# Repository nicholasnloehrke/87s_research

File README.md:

# Code and hardware design files

## Block diagram

### Overall system

> TODO

### Controller 

## Boards

### Bidirectional Load Switch

#### Known issues

- v0.1.0
    - Insufficient spacing on the AC connector 'AC\_in' net to 'earth' net
        - Workaround: Manually increase spacing
    - Lack of diode inline with 5 volt supply which would cause an issue if 5 volts and 3v3 (from ISP header) are supplied simultaneously 
        - Workaround: Don't supply both simultaneously
    - Lack of pulldown resistor on the !fault signal from the Attiny85 which could potentially have the gate driver inputs float, resulting in sporadic channel activation
        - Sporadic activation is likely only possible during power cycling as the gate drivers are internally pulled down.

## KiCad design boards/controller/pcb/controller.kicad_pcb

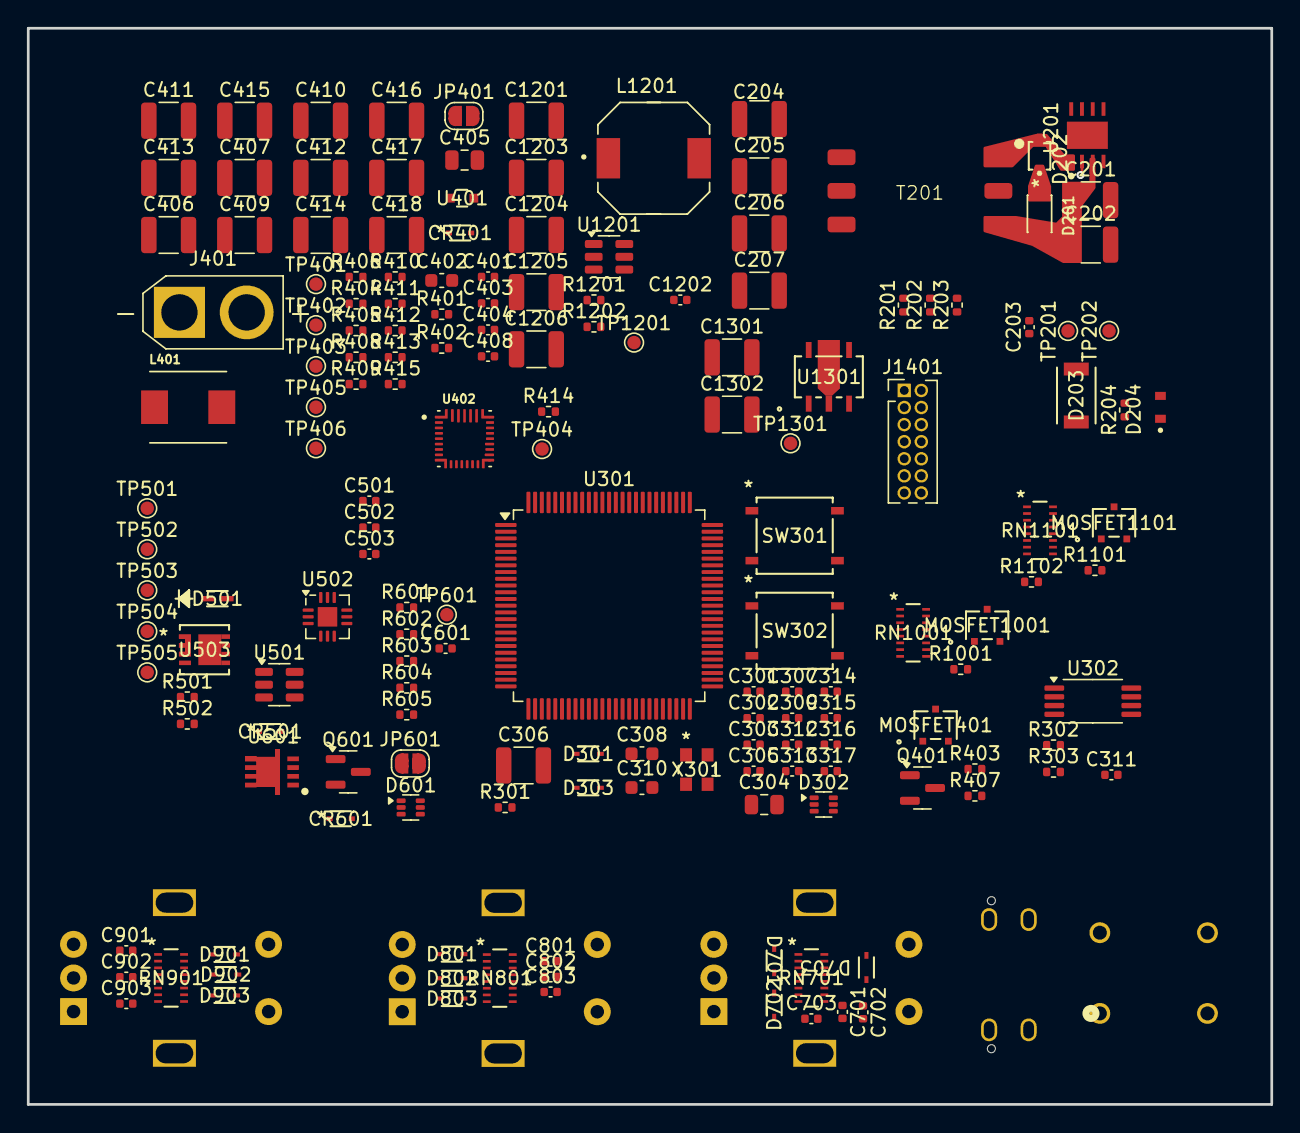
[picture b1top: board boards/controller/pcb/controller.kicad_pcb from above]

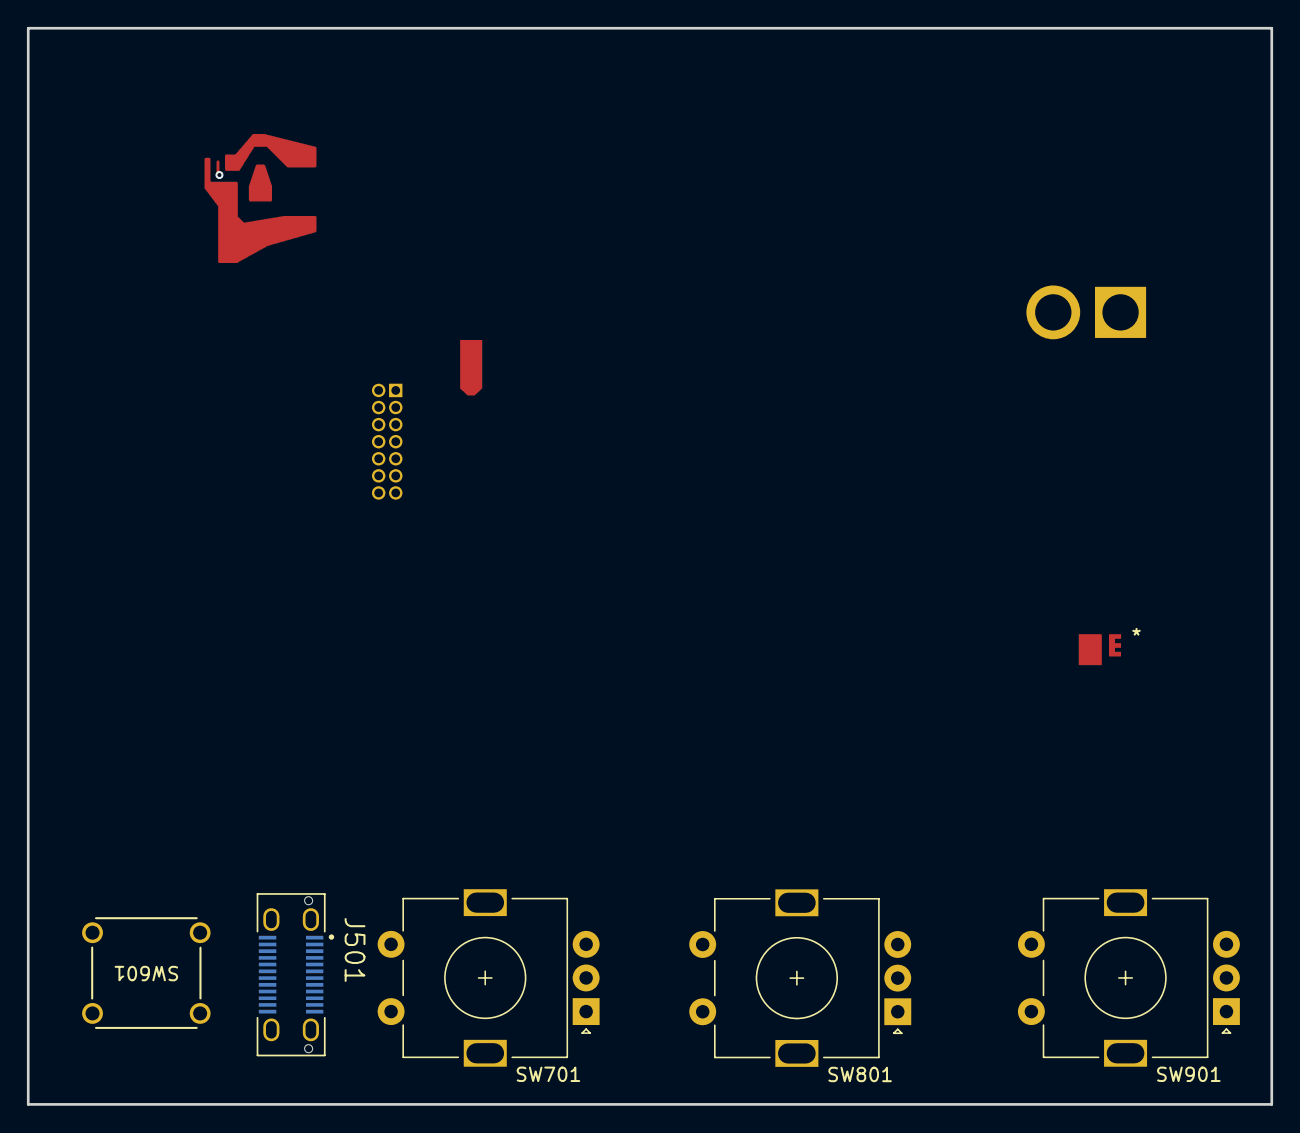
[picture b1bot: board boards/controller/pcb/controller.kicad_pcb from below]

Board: 4 copper layers, 92.4 x 80.0 mm, 170 parts (5 on the bottom side), 112 nets.

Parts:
C201, C202, C204, C205, C206, C207, C306, C406, C407, C409, C410, C411, C412, C413, C414, C415, C416, C417, C418, C1201, C1203, C1204, C1205, C1206, C1301, C1302: 10u; C_1210_3225Metric
C203, C301, C302: 26p; C_0402_1005Metric
C303, C305, C307, C309, C311, C312, C313, C314, C315, C316, C317, C401, C502, C601, C1202: 100n; C_0402_1005Metric
C304, C405: 4.7u; C_0805_2012Metric
C308, C310, C402: 1u; C_0603_1608Metric
C403, C404: 47n; C_0402_1005Metric
C408: 1n; C_0402_1005Metric
C501, C503: 330p; C_0402_1005Metric
C701, C702, C703, C801, C802, C803, C901, C902, C903: 10n; C_0402_1005Metric
CR401, CR501: PJSD24TS-AU_R1_000A1
CR601: PJSD15TS-AU_R1_000A1
D201: BZD27C27PW; BZD27C11PW
D202: CMDD4448
D203: SB54AFC-AU_R1_000A1
D204: 18V; BZT52C18K_RKG
D301, D303, D701, D702, D703, D801, D802, D803, D901, D902, D903: 3.3V; PJSD03TS-AU_R1_000A1
D302, D601: SOT-563
D501: BAT54KFILM
J401: Battery; AMASS_XT30U-F_1x02_P5.0mm_Vertical
J501: DX07S024WJ3R400; JAE_DX07S024WJ3R400
J1401: Conn_ST_STDC14; PinHeader_2x07_P1.27mm_Vertical
JP401: 3s; SolderJumper-2_P1.3mm_Open_RoundedPad1.0x1.5mm
JP601: VSYS_SW_EN; SolderJumper-2_P1.3mm_Open_RoundedPad1.0x1.5mm
L401: 1u; ASPI-0530HI-1R0M-T2
L1201: 1217AS-H-3R3N=P3; 1217AS-H-3R3N-P3
MOSFET401, MOSFET1001, MOSFET1101: SSM3J372R_LF
Q401, Q601: BSS138; SOT-23
R201, R301, R403, R404, R405, R406, R407, R408, R411, R414, R415, R501, R601, R602, R603, R605, R1001, R1102: 10k; R_0402_1005Metric
R202: 12.1k; R_0402_1005Metric
R203: 153.2k; R_0402_1005Metric
R204, R413: 100; R_0402_1005Metric
R302, R303, R401, R402: 2.2k; R_0402_1005Metric
R409, R410, R412: 6.04k; R_0402_1005Metric
R502: 600; R_0402_1005Metric
R604, R1201: 100k; R_0402_1005Metric
R1101: 220; R_0402_1005Metric
R1202: 13.7k; R_0402_1005Metric
RN701, RN801, RN901, RN1001, RN1101: 10k; YC248-JR-0710KL
SW301: PTS526 SK15 SMTR2 LFS; PTS526_SK15_SMTR2_LFS
SW302: PTS526SK15SMTR2 LFS; PTS526_SK15_SMTR2_LFS
SW601: ESE-20D443
SW701, SW801, SW901: EC11E15204A3; RotaryEncoder_Alps_EC11E-Switch_Vertical_H20mm
T201: 150u; 750315829
TP201: 15V+; TestPoint_Pad_D1.0mm
TP202: 15V-; TestPoint_Pad_D1.0mm
TP401: CHG_SCL; TestPoint_Pad_D1.0mm
TP402: CHG_SDA; TestPoint_Pad_D1.0mm
TP403: VBAT_SENSE; TestPoint_Pad_D1.0mm
TP404: STAT; TestPoint_Pad_D1.0mm
TP405: VBAT; TestPoint_Pad_D1.0mm
TP406: VSYS; TestPoint_Pad_D1.0mm
TP501: VBUSc; TestPoint_Pad_D1.0mm
TP502: CC1c; TestPoint_Pad_D1.0mm
TP503: CC2c; TestPoint_Pad_D1.0mm
TP504: FLTn; TestPoint_Pad_D1.0mm
TP505: VBUS; TestPoint_Pad_D1.0mm
TP601: VSYS_SW; TestPoint_Pad_D1.0mm
TP1201: 5V; TestPoint_Pad_D1.0mm
TP1301: 3V3; TestPoint_Pad_D1.0mm
U201: LM5181NGUR-IPC_A
U301: STM32U575VITx; LQFP-100_14x14mm_P0.5mm
U302: CAT24C256; TSSOP-8_4.4x3mm_P0.65mm
U401: 3.6; CZRU52C3V6
U402: BQ25792RQMR
U501: USBLC6-2SC6; SOT-23-6
U502: TCPP01-M12; QFN-12-1EP_3x3mm_P0.5mm_EP1.45x1.45mm
U503: ISZ065N03L5SATMA1
U601: SISA35DN-T1-GE3
U1201: LMR51430YFDDCR; SOT-23-6
U1301: NJM2884U1-33-TE1
X301: 16MHz; RH100-16.000-18-2030-EXT-TR

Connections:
3V3: C305.1, C306.1, C307.1, C308.1, C309.1, C310.1, C311.1, C312.1, C313.1, C314.1, C315.1, C316.1, C317.1, C1302.1, J1401.3 (VCC), MOSFET1001.2 (S), R302.2, R303.2, R401.2, R402.2, R415.2, R1001.2, RN701.14 (R3.2), RN701.15 (R2.2), RN701.16 (R1.2), RN801.14 (R3.2), RN801.15 (R2.2), RN801.16 (R1.2), RN901.14 (R3.2), RN901.15 (R2.2), RN901.16 (R1.2), SW302.1, SW302.2, TP1301.1, U301.6 (VBAT), U301.11 (VDD), U301.21 (VREF+), U301.22 (VDDA), U301.28 (VDD), U301.50 (VDD), U301.73 (VDDUSB), U301.75 (VDD), U301.100 (VDD), U302.8 (VCC), U1301.4 (VOUT)
5V: C1203.1, C1204.1, C1205.1, C1206.1, C1301.1, L1201.2, MOSFET1101.2 (S), R1102.2, R1201.1, TP1201.1, U1301.1 (CONTROL), U1301.5 (VIN)
/Bidirectional Load Switch Interface/CH1: RN1101.16 (R1.2), U301.26 (PA3)
/Bidirectional Load Switch Interface/CH2: RN1101.15 (R2.2), U301.25 (PA2)
/Bidirectional Load Switch Interface/CH3: RN1101.14 (R3.2), U301.24 (PA1)
/Bidirectional Load Switch Interface/CH4: RN1101.13 (R4.2), U301.23 (PA0)
/Bidirectional Load Switch Interface/CH5: RN1101.12 (R5.2), U301.5 (PE6)
/Bidirectional Load Switch Interface/CH6: RN1101.11 (R6.2), U301.4 (PE5)
/Bidirectional Load Switch Interface/CH7: RN1101.10 (R7.2), U301.61 (PD14)
/Bidirectional Load Switch Interface/CH8: RN1101.9 (R8.2), U301.62 (PD15)
/Bidirectional Load Switch Interface/ENn: MOSFET1101.1 (G), R1102.1, U301.81 (PD0)
/Bidirectional Load Switch Interface/GATE_DRV_V+: C203.1, C204.1, C205.1, C206.1, C207.1, D203.1, D204.C, TP201.1
/Bidirectional Load Switch Interface/GATE_DRV_V-: C204.2, C205.2, C206.2, C207.2, D204.A, T201.4, TP202.1
/Bidirectional Load Switch Interface/RSTn: R1101.1, U301.80 (PC12)
/Charger/ENn: R411.2, U301.18 (PC3), U402.13 (~CE)
/Charger/INTn: R415.1, U301.17 (PC2), U402.21 (~INT)
/Charger/PMID: C411.1, C413.1, C415.1, U402.29 (PMID)
/Charger/QONn: U301.29 (PA4), U402.12 (~QON)
/Charger/REGN: C405.1, R404.1, R411.1, R414.2, U402.5 (REGN), U402.17 (ILIM_HIZ)
/Charger/SCL: R402.1, TP402.1, U301.15 (PC0), U402.14 (SCL)
/Charger/SDA: R401.1, TP401.1, U301.16 (PC1), U402.15 (SDA)
/Charger/VBAT: C409.1, C410.1, CR401.1, J401.1, MOSFET401.2 (S), R406.1, R413.2, TP405.1, U402.22 (BAT), U402.23 (BAT__1)
/Charger/VBAT_SENSE: C402.1, R408.2, R409.1, R410.2, TP403.1, U301.32 (PA7), U401.1
/Charger/VBAT_SENSE_EN: Q401.1 (G), R403.1, U301.31 (PA6)
/Encoder 1/An: C701.1, RN701.11 (R6.2), U301.2 (PE3)
/Encoder 1/Bn: C702.1, RN701.12 (R5.2), U301.3 (PE4)
/Encoder 1/SWn: C703.1, RN701.8 (R8.1), U301.98 (PE1)
/Encoder 2/An: C801.1, RN801.11 (R6.2), U301.30 (PA5)
/Encoder 2/Bn: C802.1, RN801.12 (R5.2), U301.89 (PB3)
/Encoder 2/SWn: C803.1, RN801.8 (R8.1), U301.90 (PB4)
/Encoder 3/An: C901.1, RN901.11 (R6.2), U301.59 (PD12)
/Encoder 3/Bn: C902.1, RN901.12 (R5.2), U301.60 (PD13)
/Encoder 3/SWn: C903.1, RN901.8 (R8.1), U301.58 (PD11)
/Isolated Flyback/EN: R201.1, U201.4 (EN_UVLO), U301.79 (PC11)
/Isolated Flyback/FB: R203.2, U201.2 (FB)
/Isolated Flyback/SW: D202.2, R203.1, T201.1, U201.1 (SW)
/LCD Interface/3V3_SW: MOSFET1001.3 (D), RN1001.1 (R1)
/LCD Interface/ENn: MOSFET1001.1 (G), R1001.1, U301.38 (PE7)
/LCD Interface/LCD_CSn: RN1001.3 (R2.2), U301.40 (PE9)
/LCD Interface/LCD_RSTn: RN1001.4 (R3.2), U301.42 (PE11)
/LCD Interface/SD_CSn: RN1001.2 (R1.2), U301.39 (PE8)
/LCD Interface/TP_RSTn: RN1001.5 (R4.2), U301.47 (PB10)
/LCD Interface/TP_SCL: RN1001.8 (R7.2), RN1001.9 (R8.2), U301.52 (PB13)
/LCD Interface/TP_SDA: RN1001.6 (R5.2), RN1001.7 (R6.2), U301.53 (PB14)
/Microcontroller/BOOT0: D303.1, R301.1, SW302.3, SW302.4, U301.94 (PH3)
/Microcontroller/EEPROM_SCL: R302.1, U301.92 (PB6), U302.6 (SCL)
/Microcontroller/EEPROM_SDA: R303.1, U301.93 (PB7), U302.5 (SDA)
/Microcontroller/NRST: D302.6, J1401.12 (~RST)
/Microcontroller/PWR_SW_LATCH: D601.1, U301.56 (PD9)
/Microcontroller/PWR_SW_SENSEn: D601.4, U301.57 (PD10)
/Microcontroller/RCC_OSC_IN: C301.1, U301.12 (PH0), X301.1
/Microcontroller/RCC_OSC_OUT: C302.1, U301.13 (PH1), X301.3
/Microcontroller/SWCLK: J1401.6 (JCLK/SWCLK), U301.76 (PA14)
/Microcontroller/SWDIO: J1401.4 (JTMS/SWDIO), U301.72 (PA13)
/Microcontroller/TCP_DBn: U301.64 (PC7), U502.10 (DB/)
/Microcontroller/TCP_FLTn: TP504.1, U301.65 (PC8), U502.11 (FLT/)
/Microcontroller/TCP_VCC: U301.66 (PC9), U502.12 (VCC)
/Microcontroller/USART2_RX: J1401.13 (VCP_RX), U301.87 (PD6)
/Microcontroller/USART2_TX: J1401.14 (VCP_TX), U301.86 (PD5)
/Microcontroller/USB_CC1: U301.77 (PA15), U502.3 (CC1)
/Microcontroller/USB_CC2: U301.54 (PB15), U502.1 (CC2)
/Microcontroller/USB_D_N: U301.70 (PA11), U501.6 (I/O1)
/Microcontroller/USB_D_P: U301.71 (PA12), U501.4 (I/O2)
/USB-C PD/CC1c: C503.1, J501.A5 (CC1), TP502.1, U502.7 (CC1c)
/USB-C PD/CC2c: C501.1, J501.B5 (CC2), TP503.1, U502.9 (CC2c)
GND: C201.2, C202.2, C301.2, C302.2, C303.1, C304.2, C305.2, C306.2, C307.2, C308.2, C309.2, C310.2, C311.2, C312.2, C313.2, C314.2, C315.2, C316.2, C317.2, C401.2, C402.2, C405.2, C406.2, C407.2, C408.2, C409.2, C410.2, C411.2, C412.2, C413.2, C414.2, C415.2, C416.2, C417.2, C418.2, C501.2, C502.2, C503.2, C701.2, C702.2, C703.2, C801.2, C802.2, C803.2, C901.2, C902.2, C903.2, C1201.2, C1203.2, C1204.2, C1205.2, C1206.2, C1301.2, C1302.2, CR401.2, CR501.2, D301.2, D303.2, D701.2, D702.2, D703.2, D801.2, D802.2, D803.2, D901.2, D902.2, D903.2, J401.2, J501.A1 (GND), J501.A12 (GND), J501.B1 (GND), J501.B12 (GND), J501.S1 (SHIELD), J1401.5 (GND), J1401.7 (GND), Q401.2 (S), Q601.2 (S), R201.2, R202.2, R301.2, R403.2, R405.2, R409.2, R412.2, R502.2, R602.2, R603.2, R1202.2, RN1101.1 (R1.1), RN1101.2 (R2.1), RN1101.3 (R3.1), RN1101.4 (R4.1), RN1101.5 (R5.1), RN1101.6 (R6.1), RN1101.7 (R7.1), RN1101.8 (R8.1), SW301.1, SW301.2, SW601.1 (a), SW601.2 (b), SW701.C, SW701.MP, SW701.S1, SW801.C, SW801.MP, SW801.S1, SW901.C, SW901.MP, SW901.S1, U201.8 (GND), U201.9 (DAP), U301.10 (VSS), U301.19 (VSSA), U301.20 (VREF-), U301.27 (VSS), U301.49 (VSS), U301.74 (VSS), U301.99 (VSS), U302.1 (A0), U302.2 (A1), U302.3 (A2), U302.4 (GND), U401.2, U402.10 (ACDRV2), U402.11 (ACDRV1), U402.27 (GND), U501.2 (GND), U502.2 (GND), U502.13 (GND), U1201.1 (GND), U1301.2 (GND), X301.2, X301.4
unnamed: C203.2, R204.1
unnamed: C601.2, CR601.2, R604.2, R605.1, U601.4
unnamed: D201.1 (K), D202.1
unnamed: D203.2, R204.2, T201.6
unnamed: D301.1, D302.3, SW301.3, SW301.4
unnamed: D601.2, R601.2, R602.1
unnamed: J501.A6 (D+), J501.B6 (D+), U501.3 (I/O2)
unnamed: J501.A7 (D-), J501.B7 (D-), U501.1 (I/O1)
unnamed: JP401.1 (A), R410.1
unnamed: JP401.2 (B), MOSFET401.3 (D), R408.1
unnamed: MOSFET401.1 (G), R406.2, R407.1
unnamed: Q401.3 (D), R407.2
unnamed: D601.5, Q601.3 (D), R605.2
unnamed: D601.6, Q601.1 (G), R603.1
unnamed: D701.1, RN701.1 (R1.1), RN701.5 (R5.1), SW701.B
unnamed: D702.1, RN701.2 (R2.1), RN701.6 (R6.1), SW701.A
unnamed: D703.1, RN701.3 (R3.1), RN701.9 (R8.2), SW701.S2
unnamed: D801.1, RN801.1 (R1.1), RN801.5 (R5.1), SW801.B
unnamed: D802.1, RN801.2 (R2.1), RN801.6 (R6.1), SW801.A
unnamed: D803.1, RN801.3 (R3.1), RN801.9 (R8.2), SW801.S2
unnamed: D901.1, RN901.1 (R1.1), RN901.5 (R5.1), SW901.B
unnamed: D902.1, RN901.2 (R2.1), RN901.6 (R6.1), SW901.A
unnamed: D903.1, RN901.3 (R3.1), RN901.9 (R8.2), SW901.S2
unnamed: D601.3, SW601.3 (c), SW601.4 (d)
unnamed: R202.1, U201.7 (RSET)
unnamed: C303.2, D302.1, D302.2, D302.4, D302.5, U301.14 (NRST)
unnamed: C304.1, U301.48 (VCAP)
unnamed: R413.1, U402.18 (BATP)
unnamed: C403.2, U402.4 (BTST1)
unnamed: C404.2, U402.19 (BTST2)
unnamed: R412.1, U402.20 (PROG)
unnamed: C408.1, U402.24 (SDRV)
unnamed: R414.1, TP404.1, U402.1 (STAT)
unnamed: C403.1, L401.1, U402.28 (SW1)
unnamed: C404.1, L401.2, U402.26 (SW2)
unnamed: R404.2, R405.1, U402.16 (TS)
unnamed: U502.5 (GATE), U503.4
unnamed: C502.1, D501.1, U502.8 (IN_GD)
unnamed: R501.2, R502.1, U502.6 (VBUS_CTRL)
unnamed: C1202.1, U1201.6 (CB)
unnamed: R1201.2, R1202.1, U1201.4 (FB)
unnamed: C1202.2, L1201.1, U1201.2 (SW)
VBUS: C401.1, C406.1, C407.1, R601.1, TP505.1, U402.2 (VBUS), U402.3 (VBUS__1), U402.8 (VAC2), U402.9 (VAC1), U502.4 (SOURCE), U503.1, U503.2, U503.3
VBUSc: CR501.1, D501.2, J501.A4 (VBUS), J501.A9 (VBUS), J501.B4 (VBUS), J501.B9 (VBUS), R501.1, TP501.1, U503.5 (D), U503.6 (D), U503.7 (D), U503.8 (D)
VSYS: C412.1, C414.1, C416.1, C417.1, C418.1, C601.1, CR601.1, JP601.1 (A), R604.1, TP406.1, U402.25 (SYS), U601.1
VSYS_SW: C201.1, C202.1, C1201.1, D201.2 (A), JP601.2 (B), T201.3, TP601.1, U201.3 (VIN), U601.5, U1201.3 (VIN), U1201.5 (EN)

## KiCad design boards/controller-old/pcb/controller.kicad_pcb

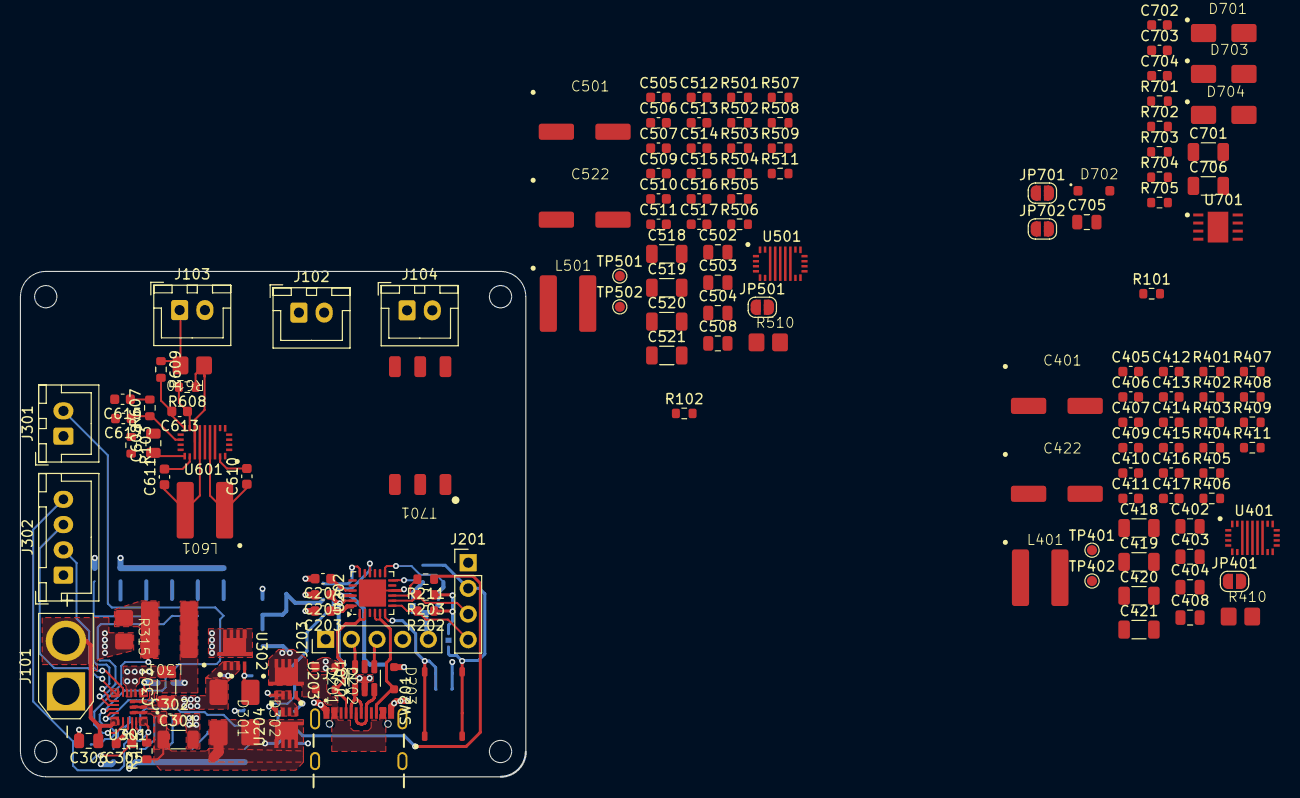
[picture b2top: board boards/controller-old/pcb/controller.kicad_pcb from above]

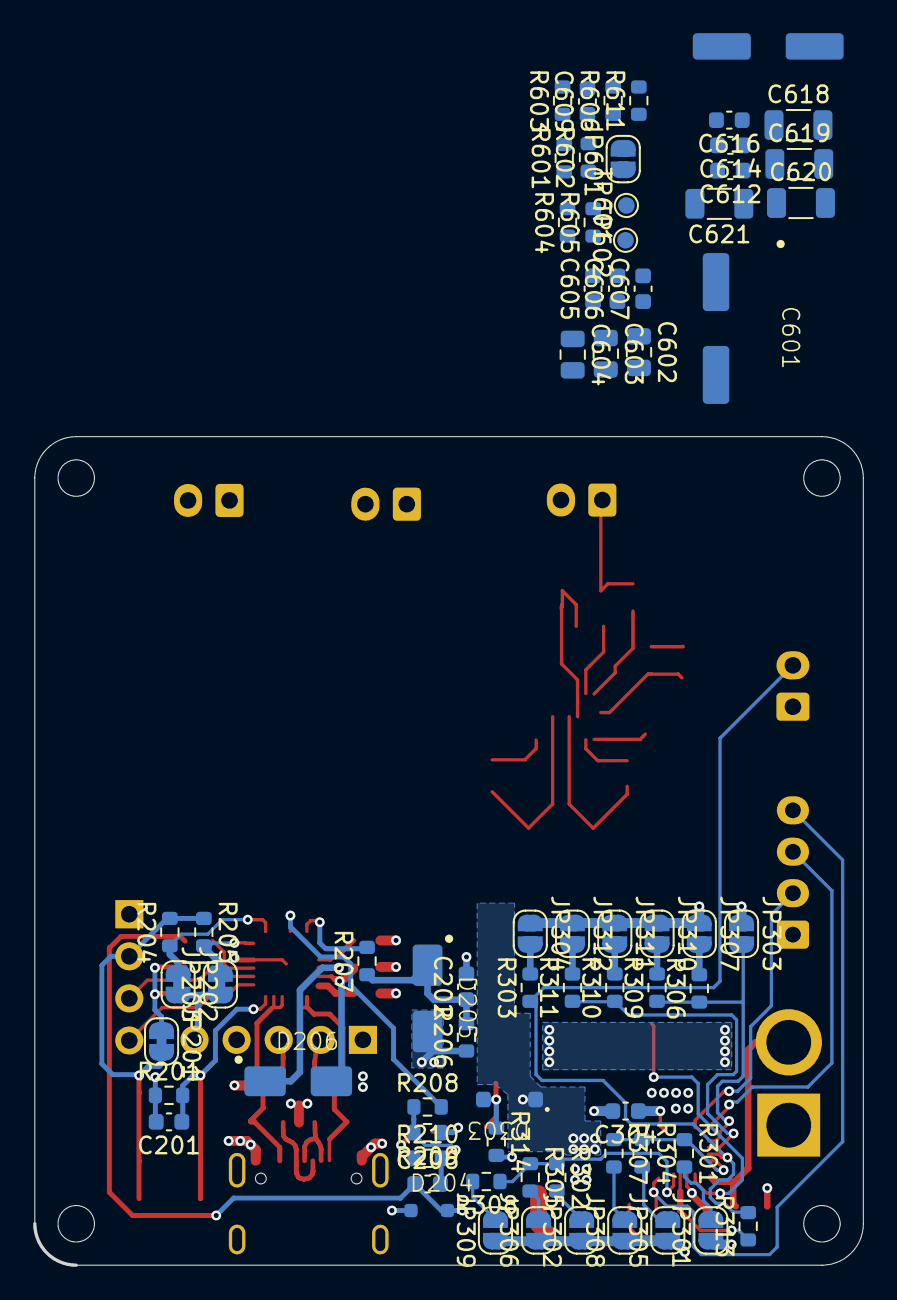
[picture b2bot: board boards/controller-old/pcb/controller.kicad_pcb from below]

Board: 4 copper layers, 50.0 x 50.0 mm, 215 parts (70 on the bottom side), 118 nets.

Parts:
C201, C206, C304, C406, C407, C410, C411, C412, C413, C414, C506, C507, C510, C511, C512, C513, C514, C606, C607, C610, C611, C612, C613, C614, C703: 100n; C_0603_1608Metric
C202, C203, C204, C205, C302, C305, C405, C416, C505, C516, C605, C616, C702: 1u; C_0603_1608Metric
C301, C418, C419, C420, C421, C518, C519, C520, C521, C618, C619, C620, C621, C701, C706: 22u; C_1206_3216Metric
C303: 2.2u; C_1206_3216Metric
C306, C402, C403, C404, C502, C503, C504, C602, C603, C604, C705: 10u; C_0805_2012Metric
C401, C422, C501, C522, C601, C622: 47u; 865080543009
C408, C508, C608: 4.7u; C_0805_2012Metric
C409, C415, C509, C515, C609, C615: 10n; C_0603_1608Metric
C417, C517, C617: 100p; C_0603_1608Metric
C704: 22p; C_0603_1608Metric
D201, D202, D203, D204: 24V; STS321240B301
D205, D206, D301, D302, D703: SK34SMA-3G
D303: 11V; BZT52C11-7-F
D701: 27V; SMAZ27-13-F
D702: 1N4148W-13-F
D704: 22V; SMAZ22-13-F
J101: Battery; AMASS_XT30U-F_1x02_P5.0mm_Vertical
J102: 5V; JST_XH_B2B-XH-A_1x02_P2.50mm_Vertical
J103: 3.3V; JST_XH_B2B-XH-A_1x02_P2.50mm_Vertical
J104: V_ISOLATED; JST_XH_B2B-XH-A_1x02_P2.50mm_Vertical
J201: Conn_01x04_Socket; PinHeader_1x04_P2.54mm_Vertical
J202: USB4105-GF-A
J203: USB IDC; PinHeader_1x05_P2.54mm_Vertical
J301: Conn_01x02_Socket; JST_XH_B2B-XH-A_1x02_P2.50mm_Vertical
J302: Conn_01x04_Socket; JST_XH_B4B-XH-A_1x04_P2.50mm_Vertical
JP201, JP202, JP203: SolderJumper_2_Bridged; SolderJumper-2_P1.3mm_Bridged_RoundedPad1.0x1.5mm
JP301, JP302: 1 Amp; SolderJumper-2_P1.3mm_Open_RoundedPad1.0x1.5mm
JP303: 1-cell series; SolderJumper-2_P1.3mm_Open_RoundedPad1.0x1.5mm
JP304: Dummy NTC; SolderJumper-2_P1.3mm_Open_RoundedPad1.0x1.5mm
JP305, JP306: 2 Amp; SolderJumper-2_P1.3mm_Open_RoundedPad1.0x1.5mm
JP307: 2-cell series; SolderJumper-2_P1.3mm_Open_RoundedPad1.0x1.5mm
JP308, JP309: 3 Amp; SolderJumper-2_P1.3mm_Open_RoundedPad1.0x1.5mm
JP310: 3-cell series; SolderJumper-2_P1.3mm_Open_RoundedPad1.0x1.5mm
JP311: 4.15 Volts; SolderJumper-2_P1.3mm_Open_RoundedPad1.0x1.5mm
JP312: 4.2 Volts; SolderJumper-2_P1.3mm_Open_RoundedPad1.0x1.5mm
JP401, JP501, JP601: EN; SolderJumper-2_P1.3mm_Open_RoundedPad1.0x1.5mm
JP701: 15 Volts; SolderJumper-2_P1.3mm_Open_RoundedPad1.0x1.5mm
JP702: 20 Volts; SolderJumper-2_P1.3mm_Open_RoundedPad1.0x1.5mm
L301: 10u; 74438367100
L401, L501, L601: 1u; 74438367010
R101, R407, R507, R607: 8.06k; R_0603_1608Metric
R102, R308: 31.6k; R_0603_1608Metric
R103: 56.2k; R_0603_1608Metric
R201, R204, R205, R209, R401, R402, R404, R405, R411, R501, R502, R504, R505, R511, R601, R602, R604, R605, R611: 100k; R_0603_1608Metric
R202, R203, R705: 2.2k; R_0603_1608Metric
R206: 470; R_0603_1608Metric
R207, R211: 1k; R_0603_1608Metric
R208: 22k; R_0603_1608Metric
R210, R704: 100; R_0603_1608Metric
R301: 80.6k; R_0603_1608Metric
R302: 95.3; R_0603_1608Metric
R303, R313: 10k; R_0603_1608Metric
R304: 40.2k; R_0603_1608Metric
R305: 47.5k; R_0603_1608Metric
R306: 35k; R_0603_1608Metric
R307: 27.4k; R_0603_1608Metric
R309, R310: 65k; R_0603_1608Metric
R311, R312: 105k; R_0603_1608Metric
R314: 1M; R_0603_1608Metric
R315, R410, R510, R610: 20m; PE1206FRE470R02L
R403, R503, R603: 9.31k; R_0603_1608Metric
R406, R506, R606: 150k; R_0603_1608Metric
R408, R409, R508, R509, R608, R609: 10; R_0603_1608Metric
R701: 12.1k; R_0603_1608Metric
R702: 153.2k; R_0603_1608Metric
R703: 203.2k; R_0603_1608Metric
SW201: PTS526 SK15 SMTR2 LFS; SMT_FS
T701: 150u; 750315829
TP401, TP402, TP501, TP502, TP601, TP602: TestPoint; TestPoint_Pad_D1.0mm
U201: USBLC6-2P6; SOT-23-6
U202: QFN-24-1EP_4x4mm_P0.5mm_EP2.7x2.7mm
U203, U204, U302: SISA35DN-T1-GE3
U301: MP2759GQ-0000-Z
U401, U501, U601: TPS552872RYQR
U701: NGU0008C-IPC_A

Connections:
/Buck-Boost-1/EN: R401.2, R402.1, U401.1 (EN/UVLO)
/Buck-Boost-1/FB_BT: R101.2, R411.1, U401.14 (FB)
/Buck-Boost-1/PG: R404.2, TP401.1, U401.3 (PG)
/Buck-Boost-1/VCC: C408.1, R404.1, R405.1, U401.2 (MODE), U401.18 (VCC)
/Buck-Boost-1/VIN: C303.1, C401.1, C402.1, C403.1, C404.1, C405.1, C406.1, C407.1, C501.1, C502.1, C503.1, C504.1, C505.1, C506.1, C507.1, C601.1, C602.1, C603.1, C604.1, C605.1, C606.1, C607.1, D301.1, D303.1, JP401.2 (B), JP501.2 (B), JP601.2 (B), U301.2 (PMID), U302.1, U401.7 (VIN), U501.7 (VIN), U601.7 (VIN)
/Buck-Boost-1/VOUT: C701.2, C702.2, C703.2, D701.2 (A), R409.1, R410.2, R411.2, T701.3, U701.3 (VIN), U701.4 (EN_UVLO)
/Buck-Boost-1/~CC: R405.2, TP402.1, U401.4 (~CC)
/Buck-Boost-2/EN: R501.2, R502.1, U501.1 (EN/UVLO)
/Buck-Boost-2/FB_BT: R102.2, R511.1, U501.14 (FB)
/Buck-Boost-2/PG: R504.2, TP501.1, U501.3 (PG)
/Buck-Boost-2/VCC: C508.1, R504.1, R505.1, U501.2 (MODE), U501.18 (VCC)
/Buck-Boost-2/VOUT: J102.1, R509.1, R510.2, R511.2
/Buck-Boost-2/~CC: R505.2, TP502.1, U501.4 (~CC)
/Buck-Boost-3/EN: R601.2, R602.1, U601.1 (EN/UVLO)
/Buck-Boost-3/FB_BT: R103.2, R611.1, U601.14 (FB)
/Buck-Boost-3/PG: R604.2, TP601.1, U601.3 (PG)
/Buck-Boost-3/VCC: C608.1, R604.1, R605.1, U601.2 (MODE), U601.18 (VCC)
/Buck-Boost-3/VOUT: J103.1, R609.1, R610.2, R611.2
/Buck-Boost-3/~CC: R605.2, TP602.1, U601.4 (~CC)
/Charger/CELL: JP303.2 (B), R306.1, R309.1, U301.10 (CELL)
/Charger/EN: J302.4, R312.2, U301.19 (VLIM)
/Charger/ILIM: R301.1, R304.1, R307.1, U301.13 (ILIM)
/Charger/ISET: R302.1, R305.1, R308.1, U301.18 (ISET)
/Charger/NTC: J301.2, R303.1, R313.2, U301.12 (NTC)
/Charger/VB: R310.1, R311.1, U301.11 (VB)
/Charger/VBATT: C306.1, J101.2, R315.2, U301.14 (BATT), U302.5
/Charger/VIN: C206.1, C301.1, C302.1, D204.2, D301.2, D302.2, R211.1, R312.1, U204.5, U301.1 (IN)
/Charger/~ACOK: J302.3, U301.9 (~ACOK)
/Charger/~STAT: J302.2, U301.8 (~STAT)
/Isolated Flyback/FB: JP701.1 (A), JP702.1 (A), U701.2 (FB)
/Isolated Flyback/SW: D702.2, R702.1, R703.1, T701.1, U701.1 (SW)
/Isolated Flyback/VOUT+: C704.2, C705.2, C706.2, D703.1, D704.1 (K), J104.1, R705.2
/Isolated Flyback/VOUT-: C705.1, C706.1, D704.2 (A), J104.2, R705.1, T701.4
/USB-C PD/ADDR0: JP203.2 (B), R205.2, U202.12 (ADDR0)
/USB-C PD/ADDR1: JP202.1 (A), R204.1, U202.13 (ADDR1)
/USB-C PD/CC1: D202.2, J202.A5 (CC1), U202.1 (CC1DB), U202.2 (CC1)
/USB-C PD/CC2: D203.2, J202.B5 (CC2), U202.4 (CC2), U202.5 (CC2DB)
/USB-C PD/D_N: J203.2, U201.6 (I/O1)
/USB-C PD/D_P: J203.3, U201.4 (I/O2)
/USB-C PD/RESET: C201.1, R201.2, SW201.1, SW201.2, U202.6 (RESET)
/USB-C PD/SCL: J201.4, R202.2, U202.7 (SCL)
/USB-C PD/SDA: J201.3, R203.2, U202.8 (SDA)
/USB-C PD/VSYS: D206.1, J201.2, JP201.2 (B), R204.2, R205.1, SW201.3, SW201.4, U202.22 (VSYS)
/USB-C PD/pre_esd_D_N: J202.A7 (D-), J202.B7 (D-), U201.1 (I/O1)
/USB-C PD/pre_esd_D_P: J202.A6 (D+), J202.B6 (D+), U201.3 (I/O2)
GND: C201.2, C202.2, C203.2, C204.2, C205.2, C301.2, C302.2, C303.2, C305.2, C306.2, C401.2, C402.2, C403.2, C404.2, C405.2, C406.2, C407.2, C408.2, C409.2, C412.2, C414.2, C415.2, C416.2, C417.2, C418.2, C419.2, C420.2, C421.2, C422.2, C501.2, C502.2, C503.2, C504.2, C505.2, C506.2, C507.2, C508.2, C509.2, C512.2, C514.2, C515.2, C516.2, C517.2, C518.2, C519.2, C520.2, C521.2, C522.2, C601.2, C602.2, C603.2, C604.2, C605.2, C606.2, C607.2, C608.2, C609.2, C612.2, C614.2, C615.2, C616.2, C617.2, C618.2, C619.2, C620.2, C621.2, C622.2, C701.1, C702.1, C703.1, D201.1, D202.1, D203.1, D204.1, J101.1, J102.2, J103.2, J201.1, J202.A1_B12 (GND), J202.B1_A12 (GND), J203.4, J203.5, J301.1, J302.1, JP202.2 (B), JP203.1 (A), JP301.1 (A), JP302.1 (A), JP303.1 (A), JP304.1 (A), JP305.1 (A), JP306.1 (A), JP307.1 (A), JP308.1 (A), JP309.1 (A), JP310.1 (A), JP311.1 (A), JP312.1 (A), R101.1, R102.1, R103.1, R201.1, R314.2, R402.2, R403.2, R406.2, R502.2, R503.2, R506.2, R602.2, R603.2, R606.2, R701.2, U201.2 (GND), U202.10 (GND), U202.25 (GND), U301.5 (PGND), U301.6 (PGND), U301.7 (PGND), U301.16 (AGND), U401.9 (PGND), U401.17 (AGND), U501.9 (PGND), U501.17 (AGND), U601.9 (PGND), U601.17 (AGND), U701.8 (GND), U701.9 (DAP)
unnamed: C202.1, D205.1, R206.2, R207.1
unnamed: C206.2, R210.2
unnamed: C415.1, R407.2
unnamed: C515.1, R507.2
unnamed: C615.1, R607.2
unnamed: C704.1, R704.2
unnamed: D302.1, D303.2, R314.1, U302.4
unnamed: D701.1 (K), D702.1
unnamed: D703.2, R704.1, T701.6
unnamed: JP201.1 (A), R202.1, R203.1
unnamed: JP301.2 (B), R301.2
unnamed: JP302.2 (B), R302.2
unnamed: JP304.2 (B), R303.2
unnamed: JP305.2 (B), R304.2
unnamed: JP306.2 (B), R305.2
unnamed: JP307.2 (B), R306.2
unnamed: JP308.2 (B), R307.2
unnamed: JP309.2 (B), R308.2
unnamed: JP310.2 (B), R309.2
unnamed: JP311.2 (B), R310.2
unnamed: JP312.2 (B), R311.2
unnamed: JP401.1 (A), R401.1
unnamed: JP501.1 (A), R501.1
unnamed: JP601.1 (A), R601.1
unnamed: JP701.2 (B), R702.2
unnamed: JP702.2 (B), R703.2
unnamed: R208.1, R209.2, R210.1, U203.4, U204.4
unnamed: R211.2, U202.9 (DISCH)
unnamed: R208.2, U202.16 (VBUS_EN_SNK)
unnamed: R207.2, U202.18 (VBUS_VS_DISCH)
unnamed: C203.1, R209.1, U202.24 (VDD), U203.1, U204.1
unnamed: C204.1, U202.21 (VREG_1V2)
unnamed: C205.1, D206.2, U202.23 (VREG_2V7)
unnamed: C304.1, U301.4 (BST)
unnamed: L301.2, R315.1, U301.15 (CSP)
unnamed: C304.2, L301.1, U301.3 (SW)
unnamed: C305.1, R313.1, U301.17 (VCC)
unnamed: C410.2, U401.20 (BOOT1)
unnamed: C411.2, U401.19 (BOOT2)
unnamed: R406.1, U401.16 (CDC)
unnamed: C417.1, R407.1, U401.15 (COMP)
unnamed: C409.1, U401.5 (DITH/SYNC)
unnamed: R403.1, U401.6 (FSW)
unnamed: C413.2, R409.2, U401.13 (ISN)
unnamed: C413.1, R408.2, U401.12 (ISP)
unnamed: C410.1, L401.1, U401.8 (SW1)
unnamed: C411.1, L401.2, U401.10 (SW2)
unnamed: C412.1, C414.1, C416.1, C418.1, C419.1, C420.1, C421.1, C422.1, R408.1, R410.1, U401.11 (VOUT)
unnamed: C510.2, U501.20 (BOOT1)
unnamed: C511.2, U501.19 (BOOT2)
unnamed: R506.1, U501.16 (CDC)
unnamed: C517.1, R507.1, U501.15 (COMP)
unnamed: C509.1, U501.5 (DITH/SYNC)
unnamed: R503.1, U501.6 (FSW)
unnamed: C513.2, R509.2, U501.13 (ISN)
unnamed: C513.1, R508.2, U501.12 (ISP)
unnamed: C510.1, L501.1, U501.8 (SW1)
unnamed: C511.1, L501.2, U501.10 (SW2)
unnamed: C512.1, C514.1, C516.1, C518.1, C519.1, C520.1, C521.1, C522.1, R508.1, R510.1, U501.11 (VOUT)
unnamed: C610.2, U601.20 (BOOT1)
unnamed: C611.2, U601.19 (BOOT2)
unnamed: R606.1, U601.16 (CDC)
unnamed: C617.1, R607.1, U601.15 (COMP)
unnamed: C609.1, U601.5 (DITH/SYNC)
unnamed: R603.1, U601.6 (FSW)
unnamed: C613.2, R609.2, U601.13 (ISN)
unnamed: C613.1, R608.2, U601.12 (ISP)
unnamed: C610.1, L601.1, U601.8 (SW1)
unnamed: C611.1, L601.2, U601.10 (SW2)
unnamed: C612.1, C614.1, C616.1, C618.1, C619.1, C620.1, C621.1, C622.1, R608.1, R610.1, U601.11 (VOUT)
unnamed: R701.1, U701.7 (RSET)
VBUS: D201.2, D205.2, J202.A4_B9 (VBUS), J202.B4_A9 (VBUS), R206.1, U203.5

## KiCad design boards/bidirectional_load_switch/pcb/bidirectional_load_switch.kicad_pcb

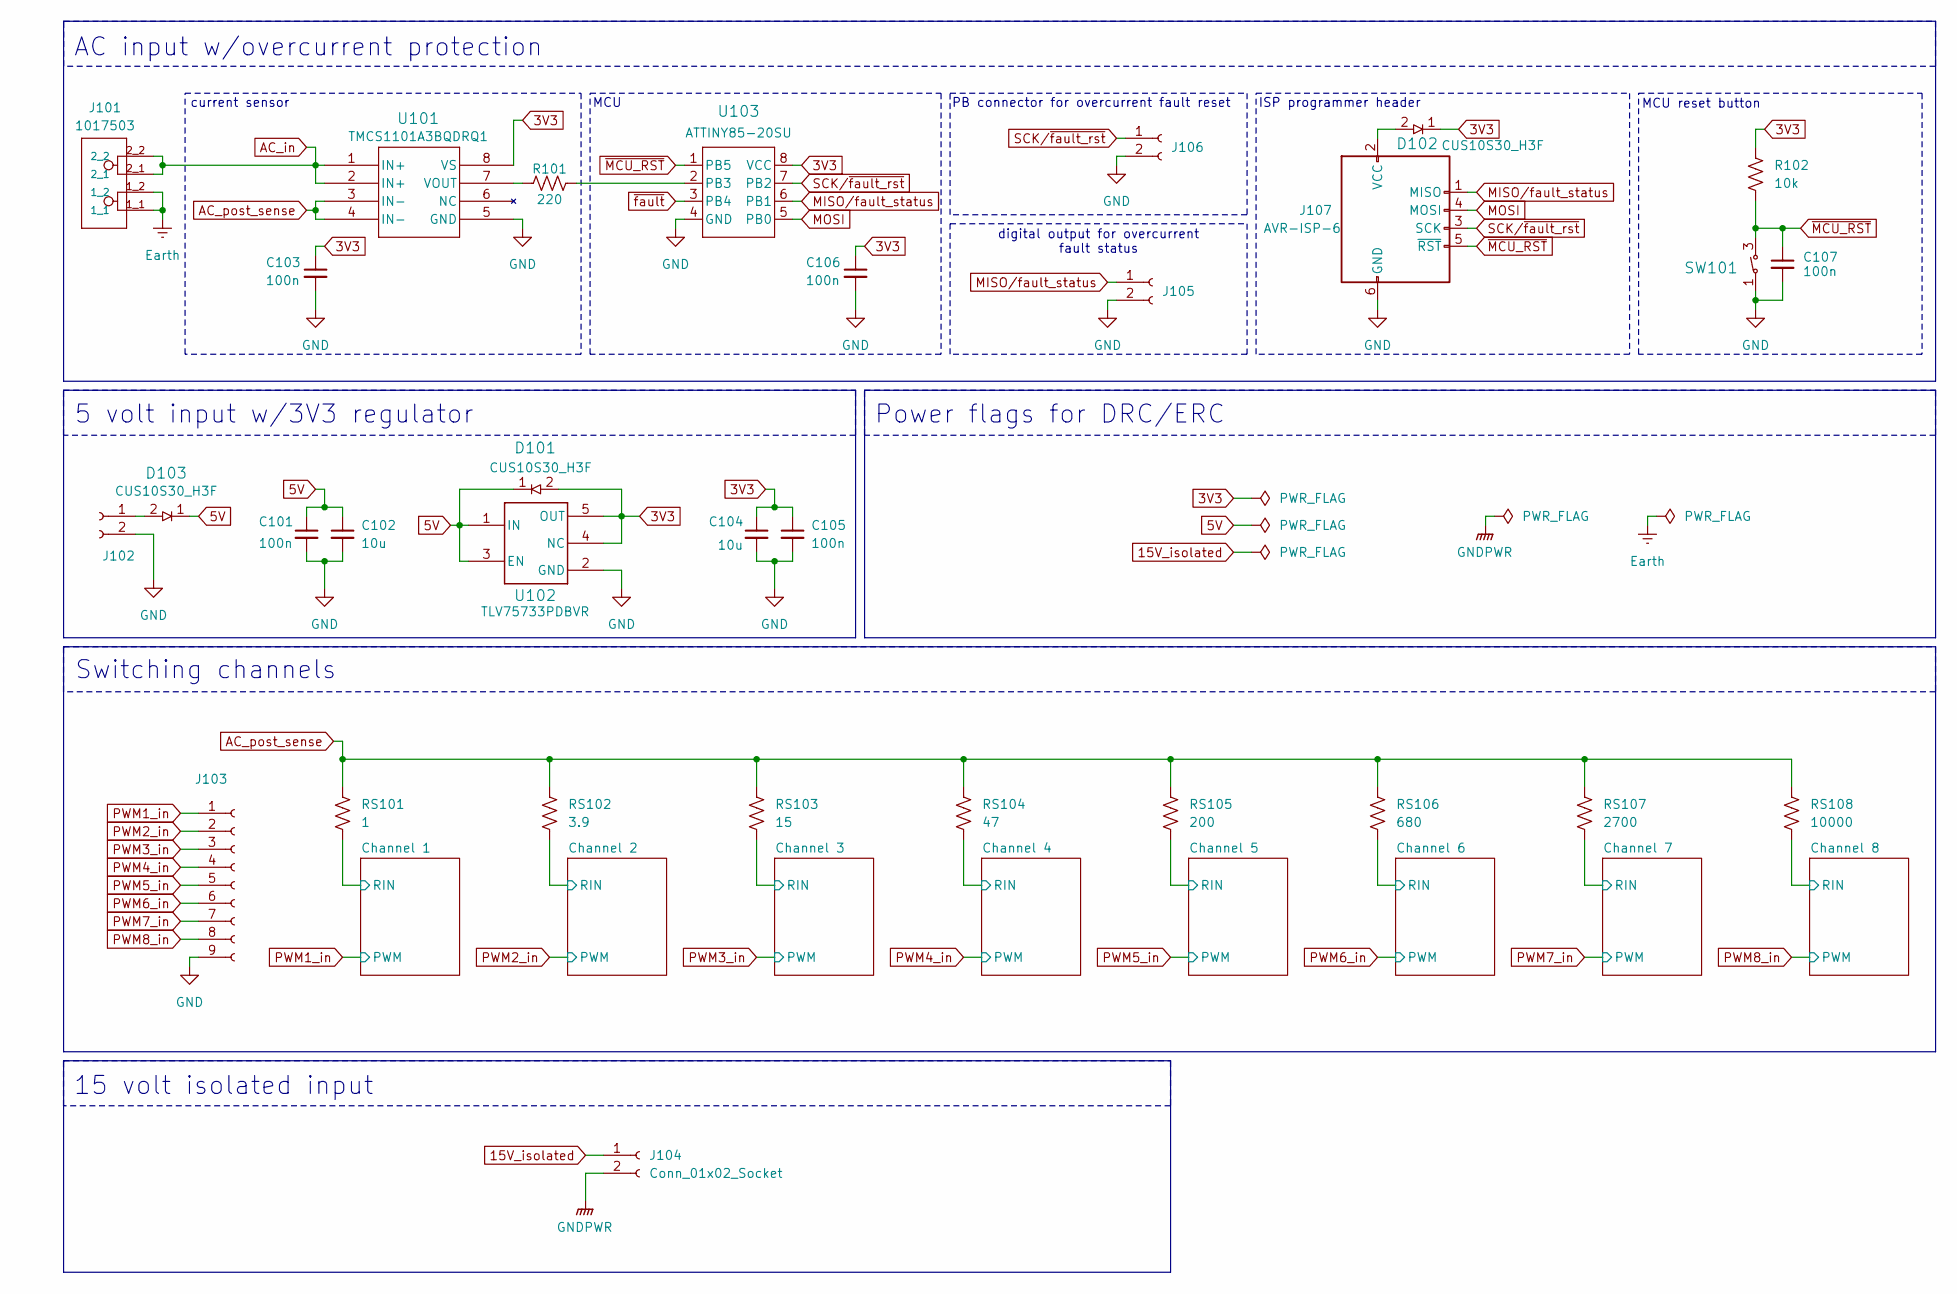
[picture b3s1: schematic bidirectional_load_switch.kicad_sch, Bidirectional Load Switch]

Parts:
C101, C103, C105, C106, C107: 100n; C_0603_1608Metric
C102, C104: 10u; C_1206_3216Metric
D101, D102, D103: USC_TOS; MPN CUS10S30_H3F
J101: PHOENIX_1017503; PARTREV 22.12.2017
J102, J104, J105, J106: Conn_01x02_Socket; PinHeader_1x02_P2.54mm_Vertical
J103: Conn_01x09_Socket; PinHeader_1x09_P2.54mm_Vertical
J107: AVR-ISP-6; IDC-Header_2x03_P2.54mm_Vertical
R101: 220; R_0603_1608Metric
R102: 10k; R_0603_1608Metric
RS101: 1; R_2512_6332Metric
RS102: 3.9; R_2512_6332Metric
RS103: 15; R_2512_6332Metric
RS104: 47; R_2512_6332Metric
RS105: 200; R_2512_6332Metric
RS106: 680; R_2512_6332Metric
RS107: 2700; R_2512_6332Metric
RS108: 10000; R_2512_6332Metric
SW101: SMT_FS; MPN PTS526 SK15 SMTR2 LFS
U101: SOIC8_D_TEX; MPN TMCS1101A3BQDRQ1
U102: DBV0005A_L; MPN TLV75733PDBVR
U103: 8S2_ATM; MPN ATTINY85-20SU

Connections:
3V3: C103.1, C104.1, C105.1, C106.1, D101.2, D102.1, R102.1, U101.8 (VS), U102.4 (NC), U102.5 (OUT), U103.8 (VCC); also elsewhere on the board
5V: C101.1, C102.1, D101.1, D103.1, U102.1 (IN), U102.3 (EN)
15V_isolated: J104.1; also elsewhere on the board
/Channel 1/RIN: RS101.2; also elsewhere on the board
/Channel 2/RIN: RS102.2; also elsewhere on the board
/Channel 3/RIN: RS103.2; also elsewhere on the board
/Channel 4/RIN: RS104.2; also elsewhere on the board
/Channel 5/RIN: RS105.2; also elsewhere on the board
/Channel 6/RIN: RS106.2; also elsewhere on the board
/Channel 7/RIN: RS107.2; also elsewhere on the board
/Channel 8/RIN: RS108.2; also elsewhere on the board
AC_in: J101.2_1, J101.2_2, U101.1 (IN+), U101.2 (IN+)
AC_post_sense: RS101.1, RS102.1, RS103.1, RS104.1, RS105.1, RS106.1, RS107.1, RS108.1, U101.3 (IN-), U101.4 (IN-)
Earth: J101.1_1, J101.1_2; also elsewhere on the board
GND: C101.2, C102.2, C103.2, C104.2, C105.2, C106.2, C107.2, J102.2, J103.9, J105.2, J106.2, J107.6 (GND), SW101.1, SW101.2, U101.5 (GND), U102.2 (GND), U103.4 (GND); also elsewhere on the board
GNDPWR: J104.2; also elsewhere on the board
MISO/fault_status: J105.1, J107.1 (MISO), U103.6 (PB1)
MOSI: J107.4 (MOSI), U103.5 (PB0)
unnamed: D103.2, J102.1
unnamed: D102.2, J107.2 (VCC)
unnamed: R101.1, U101.7 (VOUT)
unnamed: R101.2, U103.2 (PB3)
PWM1_in: J103.1; also elsewhere on the board
PWM2_in: J103.2; also elsewhere on the board
PWM3_in: J103.3; also elsewhere on the board
PWM4_in: J103.4; also elsewhere on the board
PWM5_in: J103.5; also elsewhere on the board
PWM6_in: J103.6; also elsewhere on the board
PWM7_in: J103.7; also elsewhere on the board
PWM8_in: J103.8; also elsewhere on the board
SCK/~fault_rst: J106.1, J107.3 (SCK), U103.7 (PB2)
~MCU_RST: C107.1, J107.5 (~RST), R102.2, SW101.3, SW101.4, U103.1 (PB5)
~fault: U103.3 (PB4); also elsewhere on the board

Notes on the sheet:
digital output for overcurrent fault status
PB connector for overcurrent fault reset
Power flags for DRC/ERC
MCU
Switching channels
15 volt isolated input
ISP programmer header
MCU reset button
AC input w/overcurrent protection
current sensor
5 volt input w/3V3 regulator
